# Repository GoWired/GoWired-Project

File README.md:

This is a repository for **GoWired**, RS485 & MySensors based, open source home automation hardware previously released at [openhardware.io](https://www.openhardware.io/user/2098#view=projects). Lately it took part in a successful **[crowdfunding campaign](https://www.crowdsupply.com/domatic/getwired)**. It is now available to buy at [Mouser](https://www2.mouser.com/Search/Refine?Keyword=getwired).

## Features
- MySensors library for communication through RS485 protocol,
- FOTW updates,
- Thermal and electrical security procedures,
- Easy configuration,
- Operating with ON/OFF receivers, roller shutters, dimmable LED tapes (white, RGB, RGBW),
- Buttons: long press and short press logic,
- Sensors: built-in current sensor and temperature sensor handling.

## Wiki
To learn more, have a look at our [wiki](https://github.com/feanor-anglin/GetWired-Project/wiki).

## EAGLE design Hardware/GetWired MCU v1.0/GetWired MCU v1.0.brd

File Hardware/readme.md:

All hardware schematics will be released here.

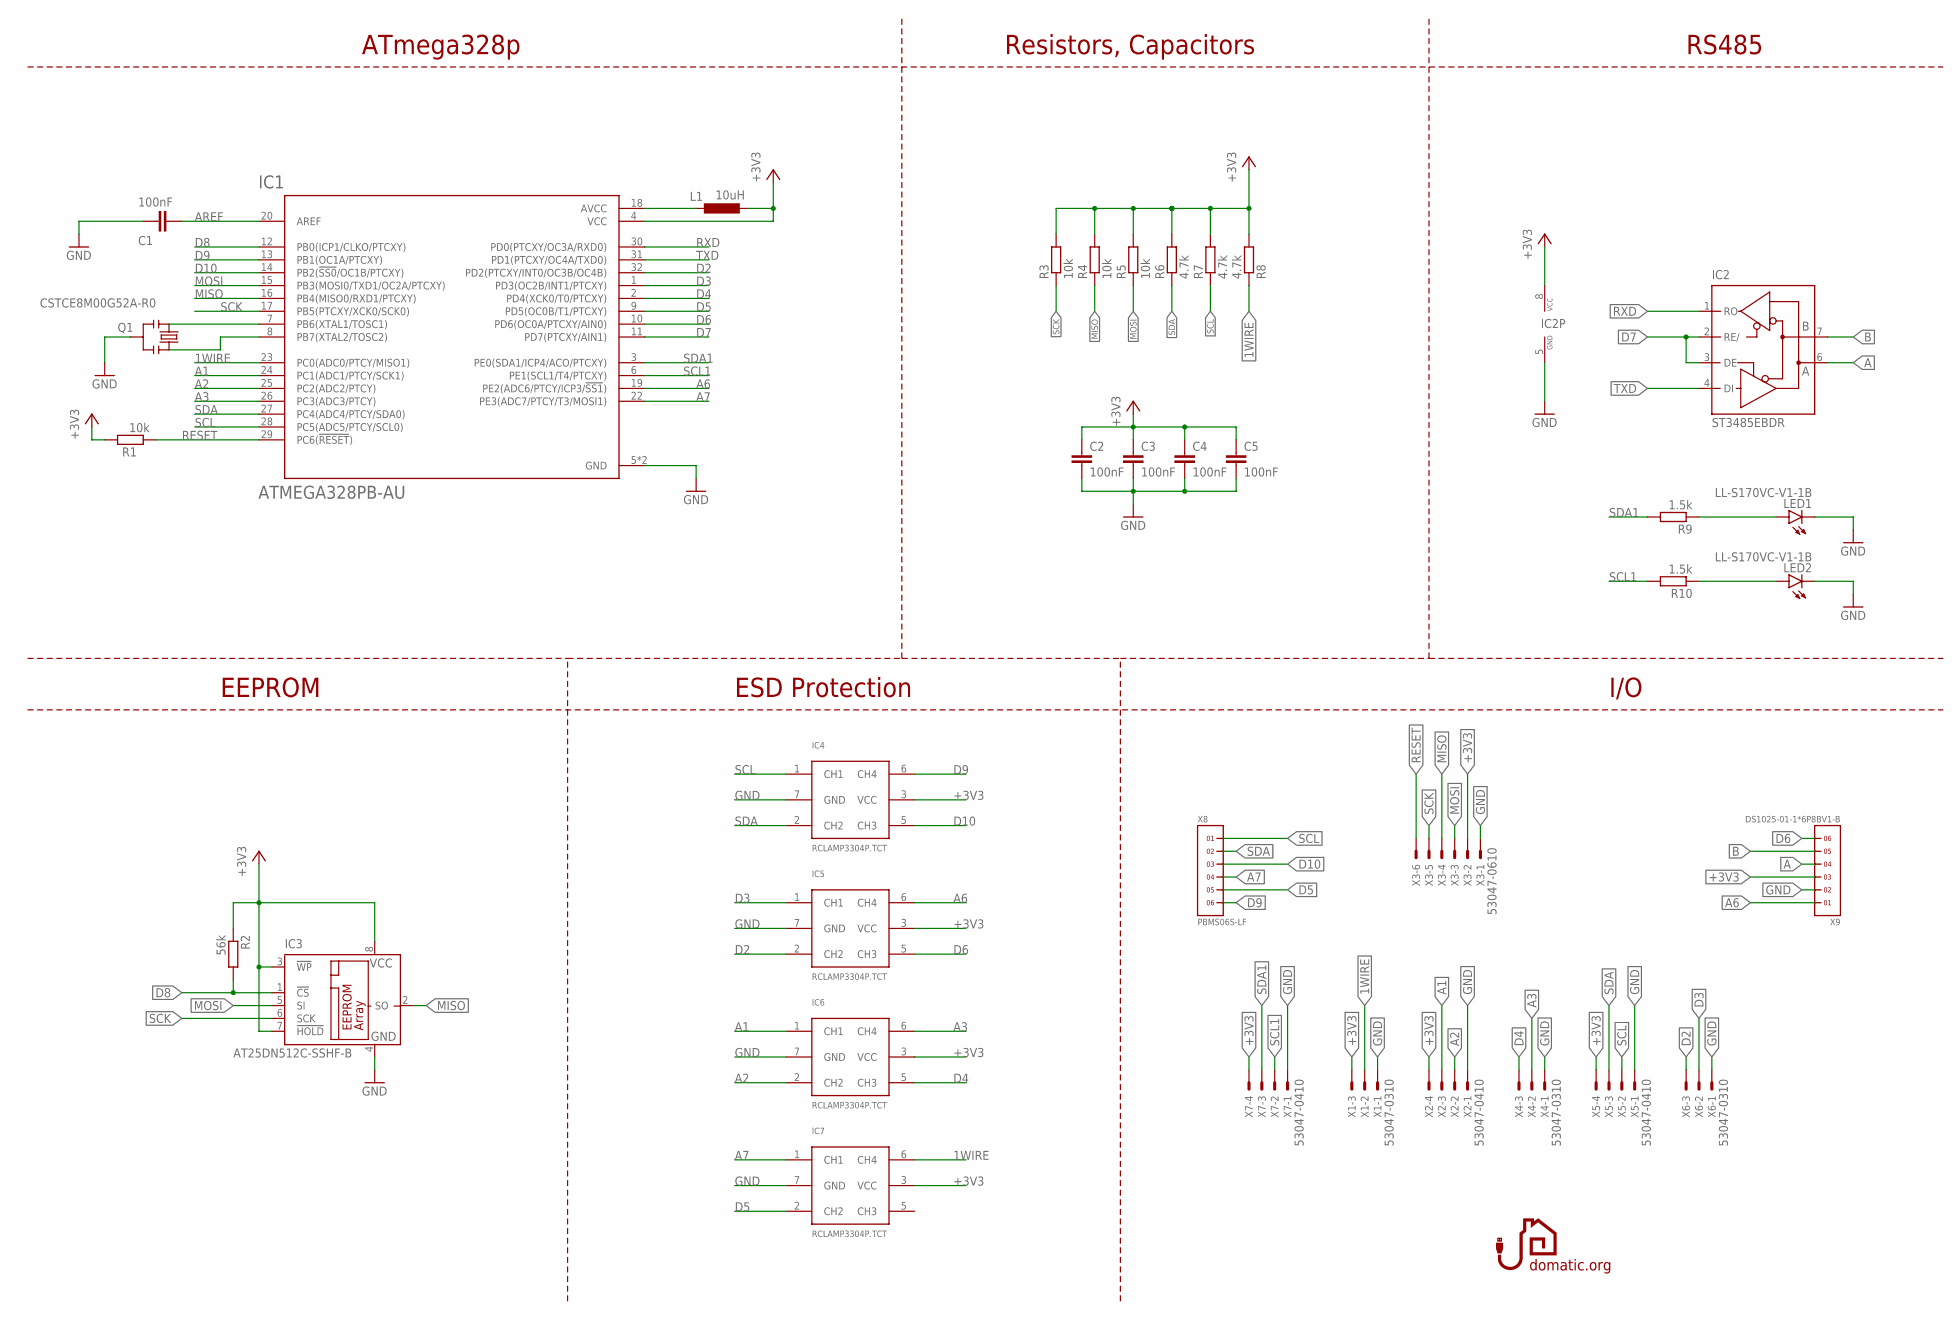
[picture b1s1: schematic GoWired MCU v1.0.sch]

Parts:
C1, C2, C3, C4, C5: 100nF; C0603
IC1: ATMEGA328PB-AU; TQFP32-08-REF
IC2: ST3485EBDR; SO08; MPN ST3485EBDR
IC3: AT25DN512C-SSHF-B; SO-08; MPN AT25DN512C-SSHF-B
IC4, IC5, IC6, IC7: RCLAMP3304P.TCT; SON50P160X160X65-7T45X130-V2
L1: 10uH; C1608
LED1, LED2: LL-S170VC-V1-1B; CHIPLED_0603
Q1: CSTCE8M00G52A-R0; CSTCE_V_C
R1, R3, R4, R5: 10k; R0603
R2: 56k; R0603
R6, R7, R8: 4.7k; R0603
R9, R10: 1.5k; R0603
X1, X4, X6: 53047-0310; 53047-03
X2, X5, X7: 53047-0410; 53047-04
X3: 53047-0610; 53047-06
X8: PBMS06S-LF; 1X6-FEMALE-LONG
X9: DS1025-01-1*6P8BV1-B; HDRV6W50P200_1X6_1200X200X600B

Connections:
1WIRE: IC1.23 (PC0(ADC0/PTCY/MISO1)), IC7.6 (CH4), R8.1, X1.2
+3V3: C2.2, C3.2, C4.1, C5.1, IC1.4 (VCC), IC2.8 (VCC), IC3.3 (!WP), IC3.7 (!HOLD), IC3.8 (VCC), IC4.3 (VCC), IC5.3 (VCC), IC6.3 (VCC), IC7.3 (VCC), L1.1, R1.2, R2.1, R3.2, R4.2, R5.2, R6.2, R7.2, R8.2, X1.3, X2.4, X3.2, X5.4, X7.4, X9.3
A: IC2.6 (A), X9.4
A1: IC1.24 (PC1(ADC1/PTCY/SCK1)), IC6.1 (CH1), X2.3
A2: IC1.25 (PC2(ADC2/PTCY)), IC6.2 (CH2), X2.2
A3: IC1.26 (PC3(ADC3/PTCY)), IC6.6 (CH4), X4.2
A6: IC1.19 (PE2(ADC6/PTCY/ICP3/!SS1!)), IC5.6 (CH4), X9.1
A7: IC1.22 (PE3(ADC7/PTCY/T3/MOSI1)), IC7.1 (CH1), X8.4
AREF: C1.2, IC1.20 (AREF)
B: IC2.7 (B), X9.5
D2: IC1.32 (PD2(PTCXY/INT0/OC3B/OC4B)), IC5.2 (CH2), X6.3
D3: IC1.1 (PD3(OC2B/INT1/PTCXY)), IC5.1 (CH1), X6.2
D4: IC1.2 (PD4(XCK0/T0/PTCXY)), IC6.5 (CH3), X4.3
D5: IC1.9 (PD5(OC0B/T1/PTCXY)), IC7.2 (CH2), X8.5
D6: IC1.10 (PD6(OC0A/PTCXY/AIN0)), IC5.5 (CH3), X9.6
D7: IC1.11 (PD7(PTCXY/AIN1)), IC2.2 (RE/), IC2.3 (DE)
D8: IC1.12 (PB0(ICP1/CLKO/PTCXY)), IC3.1 (!CS), R2.2
D9: IC1.13 (PB1(OC1A/PTCXY)), IC4.6 (CH4), X8.6
D10: IC1.14 (PB2(!SS0!/OC1B/PTCXY)), IC4.5 (CH3), X8.3
GND: C1.1, C2.1, C3.1, C4.2, C5.2, IC1.5 (GND), IC1.21 (GND), IC2.5 (GND), IC3.4 (GND), IC4.7 (GND), IC5.7 (GND), IC6.7 (GND), IC7.7 (GND), LED1.C, LED2.C, Q1.GND, X1.1, X2.1, X3.1, X4.1, X5.1, X6.1, X7.1, X9.2
MISO: IC1.16 (PB4(MISO0/RXD1/PTCXY)), IC3.2 (SO), R4.1, X3.4
MOSI: IC1.15 (PB3(MOSI0/TXD1/OC2A/PTCXY)), IC3.5 (SI), R5.1, X3.3
unnamed: LED1.A, R9.1
unnamed: IC1.7 (PB6(XTAL1/TOSC1)), Q1.X1
unnamed: IC1.8 (PB7(XTAL2/TOSC2)), Q1.X2
unnamed: IC1.18 (AVCC), L1.2
unnamed: LED2.A, R10.1
RESET: IC1.29 (PC6(!RESET!)), R1.1, X3.6
RXD: IC1.30 (PD0(PTCXY/OC3A/RXD0)), IC2.1 (RO)
SCK: IC1.17 (PB5(PTCXY/XCK0/SCK0)), IC3.6 (SCK), R3.1, X3.5
SCL: IC1.28 (PC5(ADC5/PTCY/SCL0)), IC4.1 (CH1), R7.1, X5.2, X8.1
SCL1: IC1.6 (PE1(SCL1/T4/PTCXY)), R10.2, X7.2
SDA: IC1.27 (PC4(ADC4/PTCY/SDA0)), IC4.2 (CH2), R6.1, X5.3, X8.2
SDA1: IC1.3 (PE0(SDA1/ICP4/ACO/PTCXY)), R9.2, X7.3
TXD: IC1.31 (PD1(PTCXY/OC4A/TXD0)), IC2.4 (DI)

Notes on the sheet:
ATmega328p
I/O
EEPROM
RS485
Resistors, Capacitors
ESD Protection

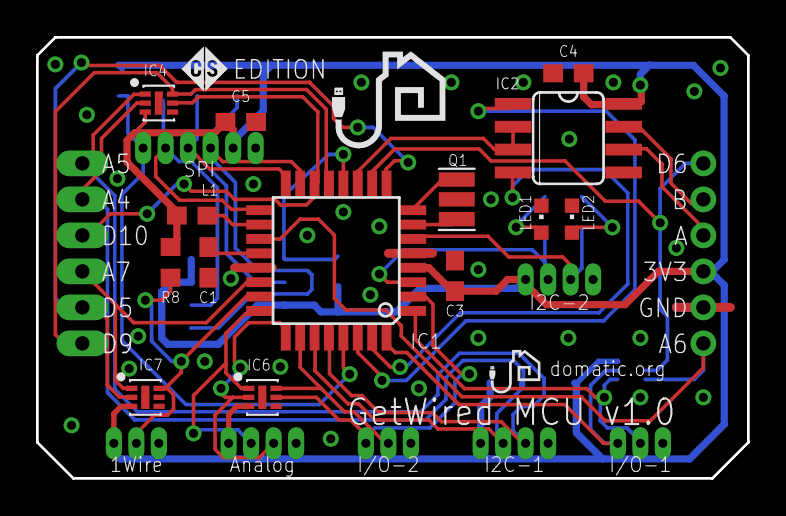
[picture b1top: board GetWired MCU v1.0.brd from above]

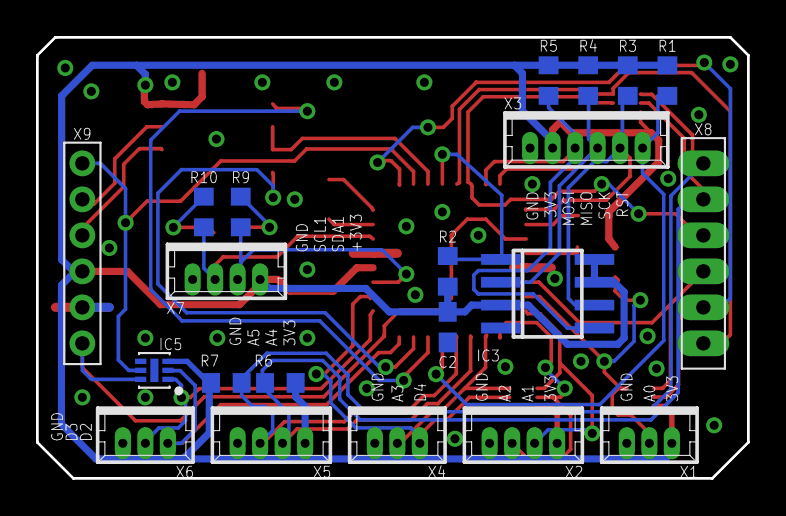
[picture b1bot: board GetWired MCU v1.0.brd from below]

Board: 2 copper layers, 39.5 x 24.5 mm, 38 parts (21 on the bottom side), 35 nets.

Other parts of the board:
U$1: CS2-2.5MM
U$2: LOGO5MMBEZ
U$3: LOGO2.5MMNAP0,8

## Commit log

2018-11-06 Create RS485_FOTW
2018-11-20 Update RS485_FOTW
2018-11-27 Rename RS485_FOTW to RS485 2SSR Shield
2018-11-27 Rename RS485_FOTW/RS485 2SSR Shield to RS485 2SSR Shield/RS485 2SSR Shield
2018-11-27 Rename RS485_FOTW/NodeDefinitions.h to RS485 2SSR Shield/NodeDefinitions.h
2018-11-27 Create RS485 4RelayDin Shield
2018-11-27 Rename RS485 4RelayDin Shield to RS485 4RelayDin Shield.ino
2018-11-27 Rename RS485 4RelayDin Shield.ino to RS485 4RelayDin Shield
2018-11-29 Update RS485 2SSR Shield
2018-11-30 Update RS485 4RelayDin Shield
2018-12-01 Create Gateway
2018-12-07 Create Roller Shutter
2018-12-07 Rename RS485 2SSR Shield/Roller Shutter to RS485 2SSR Shield RS/RollerShutter
2018-12-07 Create NodeDefinitions
2018-12-18 Update RollerShutter
2019-01-08 Update Gateway
2019-04-10 Rename NodeDefinitions to NodeDefinitions.h
2019-05-29 New firmware on the way
2019-06-28 More new files
2019-09-04 Cleaning up
2019-09-04 Improvements
2019-09-10 Configuration
2019-09-11 Bug fixes
2019-09-16 Heating Controller
2019-11-04 Fixes
2019-11-06 Rename RS485 Ethernet Gateway/Gateway to GetWired Ethernet Gateway/Gateway
2019-11-06 Rename RS485 Heating Controller/main.ino to GetWired Heating Controller/main.ino
2019-11-06 Rename GetWired Heating Controller/main.ino to RS485 Heating Controller/main.ino
2019-11-06 Rename
2019-11-06 Rename RS485_NextGen.ino to main.ino
2020-08-10 Rename BOM_Adapter GetWired v1b produkcyjna.csv to BOM GetWired Adapter v1.csv
2020-08-10 Rename PnP_Adapter GetWired v1b produkcyjna_back.csv to PnP GetWired Adapter v1.csv
2020-08-12 Newest firmware
2020-08-12 Rename Gateway to Gateway.ino
2020-08-12 Rename Gateway-MQTT to Gateway-MQTT.ino
2020-08-20 Fixes to RS autocalibration & dimmer overcurrent
2020-08-25 Fixes to handling inputs
2020-08-27 New features
2020-08-27 Rename UniversalInput.cpp to IODigital.cpp
2020-08-27 Rename UniversalInput.h to IODigital.h
2020-08-27 Minor improvements
2020-10-05 New Heating Controller software
2020-10-05 New DIN rail enclosure
    Enables mounting in-wall shields (2SSR, RGBW) on TH35 rail.
2020-10-09 Presentation delay
    Fixing issue with incorrect node presentation
2020-10-12 Thermal protection for dimmers
2020-10-12 File name fix
2020-10-12 Presentation names fix
2020-10-14 Updates to Heating Controller
2020-10-22 Init Confirmation fix
    Fixes a bug causing repetitive calling of InitConfirmation() function in case when no output configured
2020-10-22 Gateway restart fix
    Using restart button now does not restart modules connected to the gateway
2020-11-12 Rewrite Ethernet Gateway firmware
    Add watchdog and controller connection testing, minor improvements
2020-12-12 Support for DS18B20 external thermometer, refactoring
2021-03-04 Readme update
2021-05-20 Add AVR watchdog, fix roller shutter bug
2021-06-02 Remove unnecessary includes from RShutterControl.h
2021-06-08 Rewrite roller shutter operation & other changes
    - Roller shutter is now a state machine
    - No while loops in roller shutter regular operation
    - Current measurement during roller shutter movement
    - Roller shutter now reports directions of movement to the controller
    - Changes to safety procedures (thermal & electrical software fuses) and to entire main loop
    - Small improvements
2021-06-08 Bugfix
2021-06-10 Bugfix
    Fix bugs related to millis() overflow
2021-06-10 Bugfixes
2021-07-13 Reorganize folders
2021-07-13 Rename GetWired Ethernet Gateway/Gateway-MQTT.ino to Software/Ethernet Gateway/Gateway-MQTT.ino
2021-07-13 Rename GetWired Ethernet Gateway/Gateway.ino to Software/Ethernet Gateway/Gateway.ino
2021-07-13 Rename Software/Ethernet Gateway/Gateway.ino to Software/Ethernet Gateway/Gateway/Gateway.ino
2021-07-13 Rename Software/Ethernet Gateway/Gateway-MQTT.ino to Software/Ethernet Gateway/Gateway-MQTT/Gateway-MQTT.ino
2021-07-13 Rename GetWired Heating Controller/Configuration.h to Heating Controller/Configuration.h
2021-07-13 Rename Heating Controller/Configuration.h to Software/Heating Controller/Configuration.h
2021-07-13 Rename GetWired Heating Controller/main.ino to Software/Heating Controller/main/main.ino
2021-07-13 Rename Software/Heating Controller/Configuration.h to Software/Heating Controller/main/Configuration.h
2021-07-13 Rename GetWired Heating Controller/Heating.cpp to Software/Heating Controller/main/Heating.cpp
2021-07-13 Rename GetWired Heating Controller/Heating.h to Software/Heating Controller/main/Heating.h
2021-07-13 Rename GetWired New Firmware/main.ino to Software/Modules/main/main.ino
2021-07-13 Rename GetWired New Firmware/Configuration.h to Software/Modules/main/Configuration.h
2021-07-13 Rename GetWired New Firmware/Dimmer.cpp to Software/Modules/main/Dimmer.cpp
2021-07-13 Rename GetWired New Firmware/Dimmer.h to Software/Modules/main/Dimmer.h
2021-07-13 Rename GetWired New Firmware/IODigital.cpp to Software/Modules/main/IODigital.cpp
2021-07-13 Rename GetWired New Firmware/IODigital.h to Software/Modules/main/IODigital.h
2021-07-13 Rename GetWired New Firmware/InternalTemp.cpp to Software/Modules/main/InternalTemp.cpp
2021-07-13 Rename GetWired New Firmware/InternalTemp.h to Software/Modules/main/InternalTemp.h
2021-07-13 Rename GetWired New Firmware/PowerSensor.cpp to Software/Modules/main/PowerSensor.cpp
2021-07-13 Rename GetWired New Firmware/PowerSensor.h to Software/Modules/main/PowerSensor.h
2021-07-13 Rename GetWired New Firmware/RShutterControl.cpp to Software/Modules/main/RShutterControl.cpp
2021-07-13 Rename GetWired New Firmware/RShutterControl.h to Software/Modules/main/RShutterControl.h
2021-07-13 Add description to Modules software
2021-07-13 Add description to Heating Controller software
2021-07-13 Add description to Ethernet Gateway software
2021-07-13 Edit readme
2021-07-16 Add custom indication handler
2021-07-16 Use Ethernet Link Status
2021-07-19 Changes to uplink check & minor changes
2021-08-02 Add UpdateDimmer() function
2021-12-31 Change the way software handles IOs
2021-12-31 Add 8RelayDin software
2022-01-24 Relocating Multiprotocol Gateway files
2022-04-04 Changes to dimmer operation
2022-04-07 8RelayDin fixes
    Fix independent IOs, fix INPUT_TYPE issue
2022-04-08 Multiple changes
    Improvements to 8RelayDin, update for MQTT Gateway, new descriptions
2022-04-14 Improvements to 8RelayDin
    Better operation with security sensors, possibility of inverting input logic, other minor changes
2022-04-14 Add roller shutter calibration by message feature
2022-04-15 Change messages names to more descriptive
2022-04-20 Bugfix for 8RelayDin
2022-04-20 Modules software reading inputs bugfix
2022-04-27 Create GoWired-lib directory & readme file
2022-04-27 Populate GoWired-lib directory with shared library files
2022-04-27 Move GoWired-Touch software to GoWired-Project repo
2022-04-27 Remove class files from 'main' catalogues
2022-04-27 Adjust 8RelayDin software, add some documentation
2022-04-27 Adjust Heating Controller software, add some documentation and wdt
2022-04-27 Adjust 'Modules' main and add some documentation
2022-04-27 Add GoWired-lib description files
2022-04-29 Adjust Shutters library & Modules main.ino
2022-04-29 Fix IO bug
    Bug caused module slow response in certain conditions
2022-04-29 Adjust GoWired-lib folders, edit library.properties
2022-05-09 Adjust software to work with GoWired-lib
2022-05-25 Change configuration by message to work on V_TEXT message type
2022-06-06 Fix CommonIO bug, add dependencies to library properties
2022-06-15 Fix directory name
2022-06-15 Add configuration sensor to configure modules with text messages
    This feature can use notify.mysensors service in Home Assistant. First working command is "cmd1" which induces shutter calibration.
2022-06-15 Add delay when changing shutter movement direction
2022-06-15 Improve blinds/shutters handling procedure
2022-07-18 Move GoWired-lib files to separate repository
2022-07-19 Rename some files
2022-07-19 Modify Heating Controller software to work with GoWired-lib
2022-07-20 Modify includes according to what new architecture requires
2023-01-23 Update version
2023-01-23 Add second Longpress; in Touch change order of handling longpress
2023-01-24 Refactor and changes to reporting power sensor values
    Report changes bigger than 100 mA (Modules&Touch); report periodically redardless of value (Touch)
2023-01-24 Refactor UpdateIO
2023-01-24 Turn relay off if shutter is not moving
    Modules & Touch
2023-06-23 Add touch fields calibration by message feature
2023-06-23 Add watchdog test procedure / module restart by message feature
2023-06-23 Add roller shutter stopping before touch field calibration
2023-06-26 New feature: utilize unused touch field for buttons calibration
    Change some special button (long press) logic; special buttons now send false after 100 ms
2023-07-04 Bugfixes and new message for text sensor
    Type 'cmd4' to erase EEPROM and restart the module
2023-07-05 Adjust Modules code to recent Touch mods
    Additional options for configuration by message and changes to roller shutter operation
